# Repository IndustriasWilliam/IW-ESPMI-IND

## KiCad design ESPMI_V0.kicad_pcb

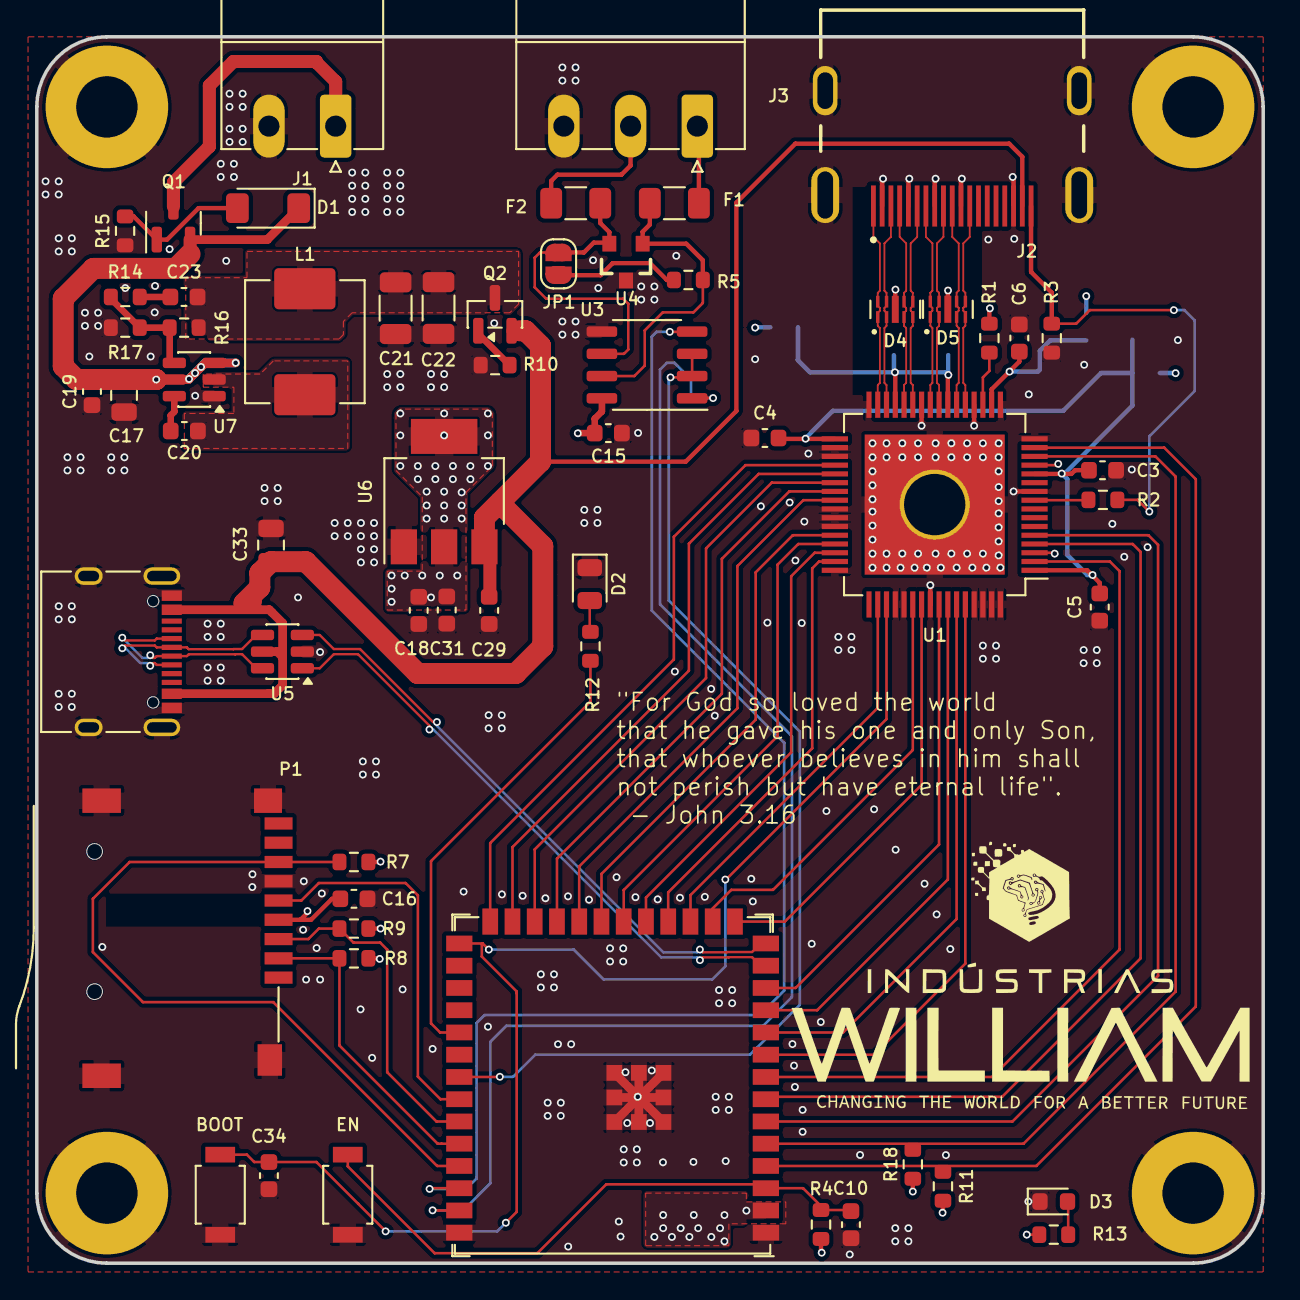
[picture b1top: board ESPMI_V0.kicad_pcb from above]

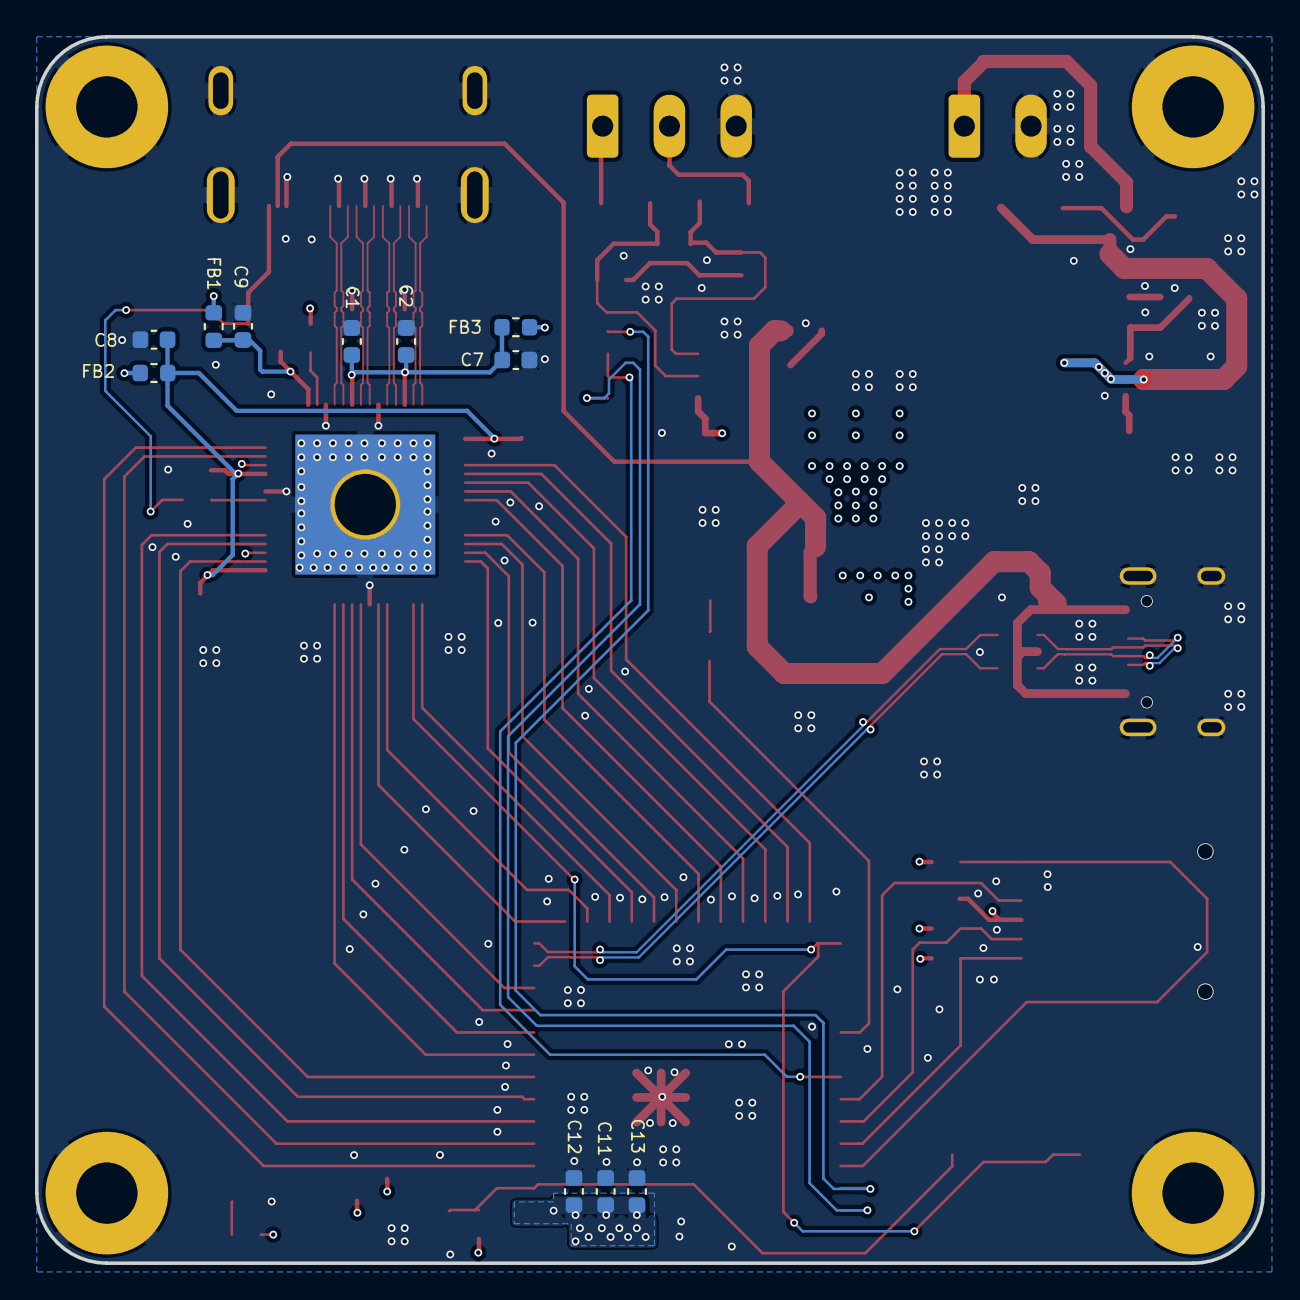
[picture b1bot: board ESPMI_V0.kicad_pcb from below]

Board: 4 copper layers, 70.0 x 70.0 mm, 75 parts (11 on the bottom side), 68 nets.

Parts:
C1, C2, C3, C4, C5, C6, C12, C15, C16, C19, C20, C29, C31, C34: 100nF; C_0603_1608Metric
C7, C8, C9, C13, C18: 10uF; C_0603_1608Metric
C10, C11: 1uF; C_0603_1608Metric
C17, C33: 10uF; C_0805_2012Metric
C21, C22: 22uF; C_1206_3216Metric
C23: 10pF; C_0603_1608Metric
D1: BZV55B7V5; D_MiniMELF
D2: LED; LED_0805_2012Metric
D3: LED; LED_0603_1608Metric
D4, D5: CDDFN10-0524P; TVS_CDDFN10-0524P
F1, F2: Polyfuse_Small; Fuse_1206_3216Metric
FB1, FB2, FB3: 600R; L_0603_1608Metric
H1, H2, H3, H4: MountingHole_Pad; MountingHole_3.5mm_Pad
J1: Screw_Terminal_01x02; PhoenixContact_MC_1,5_2-G-3.81_1x02_P3.81mm_Horizontal
J2: HDMI_A_1.4; SAMTEC_HDMR-19-01-S-SM
J3: Screw_Terminal_01x03; PhoenixContact_MC_1,5_3-G-3.81_1x03_P3.81mm_Horizontal
J5: USB_C_Receptacle_USB2.0; USB_C_Receptacle_XKB_U262-16XN-4BVC11
JP1: Jumper_2_Open; SolderJumper-2_P1.3mm_Open_RoundedPad1.0x1.5mm
L1: 6.8uH; L_APV_APH0640
P1: ST-TF-003A; SUNTECH_ST-TF-003A
Q1, Q2: AO3401A; SOT-23
R1: 510R; R_0603_1608Metric
R2: 1k; R_0603_1608Metric
R3, R15, R16: 100k; R_0603_1608Metric
R4, R7, R8, R9, R10, R14: 10k; R_0603_1608Metric
R5: 120R; R_0603_1608Metric
R11, R18: 2.2k; R_0603_1608Metric
R12, R13: 470R; R_0603_1608Metric
R17: 13.7k; R_0603_1608Metric
SW1, SW2: SW_Push; SW_SPST_B3U-1000P
U1: TFP410PAP; HTQFP-64-1EP_10x10mm_P0.5mm_EP8x8mm_Mask4.4x4.4mm_ThermalVi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
U2: ESP32-S3-WROOM-1; ESP32-S3-WROOM-1U
U3: MAX3485; SO-8_3.9x4.9mm_P1.27mm
U4: PSM712; SOT23-3
U5: USBLC6-2SC6; SOT-23-6
U6: AMS1117-3.3; SOT-223-3_TabPin2
U7: LMR51430; SOT-23-6

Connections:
+3.3V: C11.2, C12.2, C13.2, C15.2, C16.1, C18.1, C31.1, FB1.1, FB2.1, FB3.1, P1.4 (VDD), R1.2, R4.1, R7.1, R8.1, R9.1, R11.1, R13.1, R18.1, U1.3 (VREF), U1.13 (ISEL/~RST), U2.2 (3V3), U3.8 (VCC), U6.2 (VO)
+5VP: C29.1, C33.1, J2.18 (+5V), J5.A4 (VBUS), J5.A9 (VBUS), J5.B4 (VBUS), J5.B9 (VBUS), Q2.2 (S), U5.5 (VBUS), U6.3 (VI)
/LCD_B3: U1.60 (DATA3), U2.9 (GPIO16/U0CTS/ADC2_CH5/XTAL_32K_N)
/LCD_B4: U1.59 (DATA4), U2.10 (GPIO17/U1TXD/ADC2_CH6)
/LCD_B5: U1.58 (DATA5), U2.11 (GPIO18/U1RXD/ADC2_CH7/CLK_OUT3)
/LCD_B6: U1.55 (DATA6), U2.15 (GPIO3/TOUCH3/ADC1_CH2)
/LCD_B7: U1.54 (DATA7), U2.16 (GPIO46)
/LCD_DE: U1.2 (DE), U2.8 (GPIO15/U0RTS/ADC2_CH4/XTAL_32K_P)
/LCD_G3: U1.50 (DATA11), U2.17 (GPIO9/TOUCH9/ADC1_CH8/FSPIHD/SUBSPIHD)
/LCD_G4: U1.47 (DATA12), U2.18 (GPIO10/TOUCH10/ADC1_CH9/FSPICS0/FSPIIO4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)
/LCD_G5: U1.46 (DATA13), U2.19 (GPIO11/TOUCH11/ADC2_CH0/FSPID/FSPIIO5/S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)
/LCD_G6: U1.45 (DATA14), U2.20 (GPIO12/TOUCH12/ADC2_CH1/FSPICLK/FSPIIO6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)
/LCD_G7: U1.44 (DATA15), U2.21 (GPIO13/TOUCH13/ADC2_CH2/FSPIQ/FSPIIO7/S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)
/LCD_HSYNC: U1.5 (VSYNC), U2.6 (GPIO6/TOUCH6/ADC1_CH5)
/LCD_PCLK: U1.57 (IDCK+), U2.12 (GPIO8/TOUCH8/ADC1_CH7/SUBSPICS1)
/LCD_R3: U1.40 (DATA19), U2.22 (GPIO14/TOUCH14/ADC2_CH3/FSPIWP/FSPIDQS/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)
/LCD_R4: U1.39 (DATA20), U2.23 (GPIO21)
/LCD_R5: U1.38 (DATA21), U2.24 (GPIO47/SPICLK_P/SUBSPICLK_P_DIFF)
/LCD_R6: U1.37 (DATA22), U2.25 (GPIO48/SPICLK_N/SUBSPICLK_N_DIFF)
/LCD_R7: U1.36 (DATA23), U2.26 (GPIO45)
/LCD_VSYNC: U1.4 (HSYNC), U2.7 (GPIO7/TOUCH7/ADC1_CH6)
/MCU/GPIO1: U2.39 (GPIO1/TOUCH1/ADC1_CH0), U3.1 (RO)
/MCU/GPIO2: U2.38 (GPIO2/TOUCH2/ADC1_CH1), U3.4 (DI)
/MCU/GPIO38: R12.1, U2.31 (GPIO38/FSPIWP/SUBSPIWP)
/MCU/GPIO40: U2.33 (MTDO/GPIO40/CLK_OUT2), U3.2 (~RE), U3.3 (DE)
/MCU_SCL: R11.2, U1.15 (BSEL/SCL), U2.4 (GPIO4/TOUCH4/ADC1_CH3)
/MCU_SDA: R18.2, U1.14 (DSEL/SDA), U2.5 (GPIO5/TOUCH5/ADC1_CH4)
/SPI_CLK: P1.5 (CLK), U2.34 (MTDI/GPIO41/CLK_OUT1)
/SPI_CS: P1.2 (DAT3), R8.2, U2.36 (U0RXD/GPIO44/CLK_OUT2)
/SPI_MISO: P1.7 (DAT0), R7.2, U2.37 (U0TXD/GPIO43/CLK_OUT1)
/SPI_MOSI: P1.3 (CMD), R9.2, U2.35 (MTMS/GPIO42)
/USB/USB_N: J5.A7 (D-), J5.B7 (D-), U5.6 (I/O1)
/USB/USB_P: J5.A6 (D+), J5.B6 (D+), U5.4 (I/O2)
/USBD_N: U2.13 (GPIO19/U1RTS/ADC2_CH8/CLK_OUT2/USB_D-), U5.1 (I/O1)
/USBD_P: U2.14 (GPIO20/U1CTS/ADC2_CH9/CLK_OUT1/USB_D+), U5.3 (I/O2)
BOOT: C34.2, SW2.2, U1.51 (DATA10), U2.27 (GPIO0/BOOT)
ESP_EN: C10.2, R4.2, SW1.2, U2.3 (EN)
GND: C1.1, C2.1, C3.1, C4.1, C5.1, C6.2, C7.1, C8.1, C9.1, C10.1, C11.1, C12.1, C13.1, C15.1, C16.2, C17.2, C18.2, C19.2, C21.1, C22.1, C29.2, C31.2, C33.2, C34.1, D2.1 (K), D3.1 (K), D4.3_8, D5.3_8, H1.1, H2.1, H3.1, H4.1, J1.2, J2.2 (D2S), J2.5 (D1S), J2.8 (D0S), J2.11 (CKS), J2.17 (GND), J2.SH, J3.3, J5.A1 (GND), J5.A12 (GND), J5.B1 (GND), J5.B12 (GND), J5.S1 (SHIELD), P1.6 (VSS), P1.G1 (GND), P1.G2 (GND), P1.G3 (GND), P1.G4 (GND), R3.1, R10.2, R15.2, R17.1, SW1.1, SW2.1, U1.10 (~PD), U1.16 (DGND), U1.17 (PGND), U1.20 (TGND), U1.26 (TGND), U1.32 (TGND), U1.34 (RESERVED), U1.35 (DKEN), U1.41 (DATA18), U1.42 (DATA17), U1.43 (DATA16), U1.48 (DGND), U1.52 (DATA9), U1.53 (DATA8), U1.56 (IDCK-), U1.61 (DATA2), U1.62 (DATA1), U1.63 (DATA0), U1.64 (DGND), U1.65 (EP), U2.1 (GND), U2.40 (GND), U2.41 (GND), U3.5 (GND), U4.3, U5.2 (GND), U6.1 (GND), U7.1 (GND)
HTPLG: J2.19 (HPD/HEAC-), R2.1, R3.2
unnamed: C1.2, C2.2, C7.2, FB3.2, U1.23 (TVDD), U1.29 (TVDD)
unnamed: C3.2, C4.2, C5.2, C8.2, FB2.2, U1.1 (DVDD), U1.12 (DVDD), U1.33 (DVDD)
unnamed: C23.1, R14.2
unnamed: D1.2 (A), Q1.1 (G), R15.1
unnamed: C17.1, C19.1, D1.1 (K), Q1.2 (S), U7.3 (VIN), U7.5 (EN)
unnamed: D2.2 (A), R12.2
unnamed: D3.2 (A), R13.2
unnamed: J1.1, Q1.3 (D)
unnamed: F1.2, J3.1
unnamed: F2.2, J3.2
unnamed: JP1.1 (A), R5.1
unnamed: F2.1, JP1.2 (B), U3.6 (A), U4.2
unnamed: C21.2, C22.2, C23.2, L1.2, Q2.3 (D), R16.2
unnamed: Q2.1 (G), R10.1
unnamed: R2.2, U1.9 (EDGE/HTPLG)
unnamed: C6.1, C9.2, FB1.2, U1.18 (PVDD)
unnamed: R1.1, U1.19 (TFADJ)
unnamed: F1.1, R5.2, U3.7 (B), U4.1
unnamed: C20.1, U7.6 (CB)
unnamed: R14.1, R16.1, R17.2, U7.4 (FB)
unnamed: C20.2, L1.1, U7.2 (SW)
TX0_N: D5.2, D5.9, J2.9 (D0-), U1.24 (TX0-)
TX0_P: D5.1, D5.10, J2.7 (D0+), U1.25 (TX0+)
TX1_N: D4.5, D4.6, J2.6 (D1-), U1.27 (TX1-)
TX1_P: D4.4, D4.7, J2.4 (D1+), U1.28 (TX1+)
TX2_N: D4.2, D4.9, J2.3 (D2-), U1.30 (TX2-)
TX2_P: D4.1, D4.10, J2.1 (D2+), U1.31 (TX2+)
TXC_N: D5.5, D5.6, J2.12 (CK-), U1.21 (TXC-)
TXC_P: D5.4, D5.7, J2.10 (CK+), U1.22 (TXC+)
